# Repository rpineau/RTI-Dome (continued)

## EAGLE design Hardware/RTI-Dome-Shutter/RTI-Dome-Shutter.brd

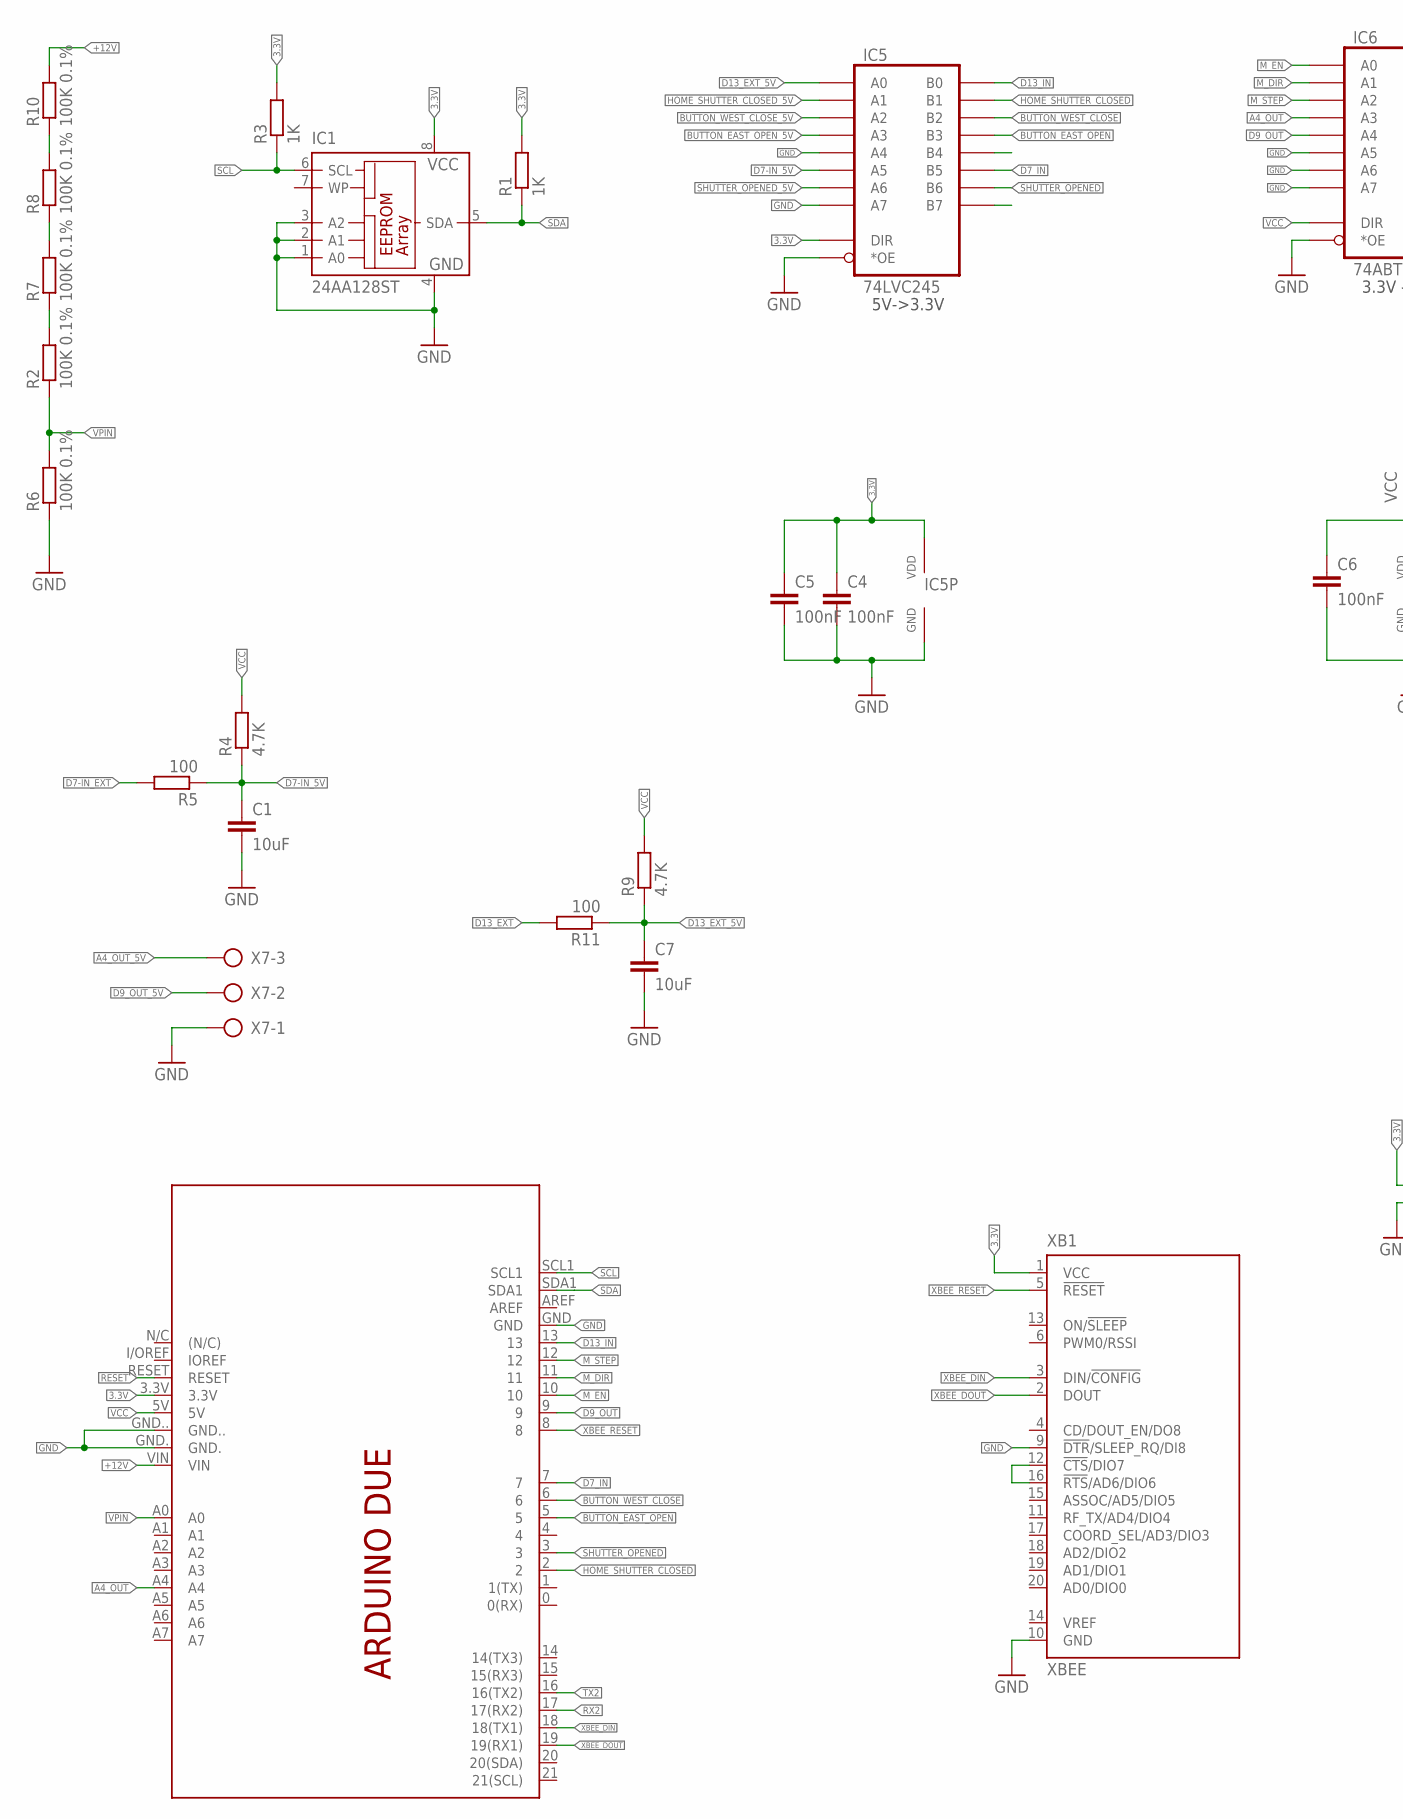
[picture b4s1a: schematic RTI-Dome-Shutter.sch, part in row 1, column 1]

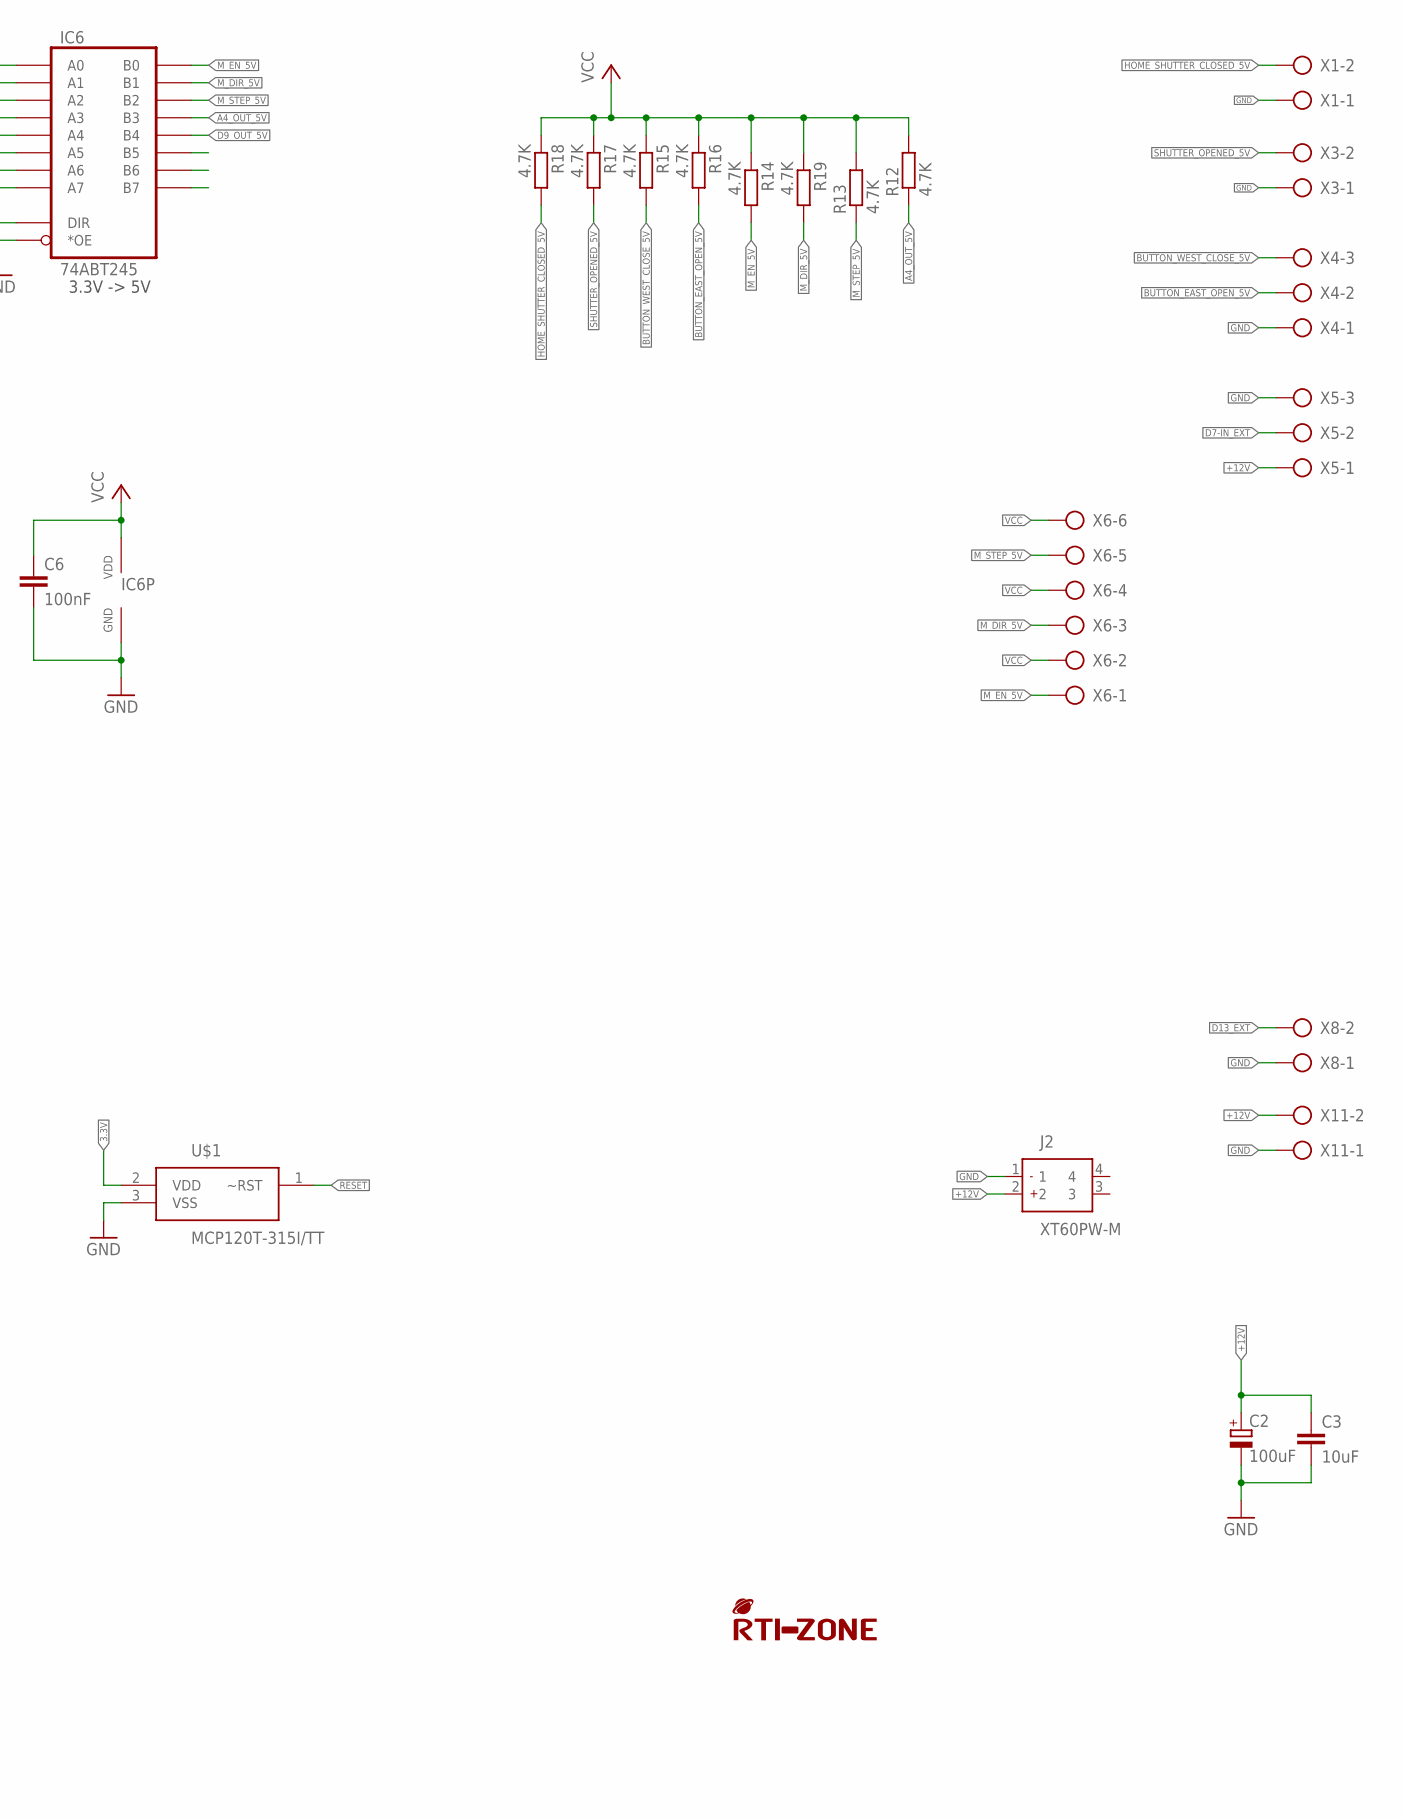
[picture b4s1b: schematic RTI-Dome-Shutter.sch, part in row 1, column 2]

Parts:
C1, C3, C7: 10uF; C0805
C2: 100uF; UD-10X10_NICHICON
C4, C5, C6: 100nF; C0805
IC1: 24AA128ST; TSSOP8
IC5: 74LVC245; TSSOP20
IC6: 74ABT245; TSSOP20
J2: XT60PW-M; XT60PWM
PCB1: ARDUINO_DUE_SHIELD_SHORT
R1, R3: 1K; R0805
R2, R6, R7, R8, R10: 100K 0.1%; R0805
R4, R9, R12, R13, R14, R15, R16, R17, R18, R19: 4.7K; R0805
R5, R11: 100; R0805
U$1: MCP120T-315I/TT; SOT95P237X112-3N; MPN MCP120T-315I/TT
U$4: RTI-LOGO_BIG; LOGO_BIG
X1, X3, X8, X11: AK500/2
X4, X5, X7: AK500/3
X6: AK500/6
XB1: XBEE

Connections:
3.3V: C4.1, C5.1, IC1.8 (VCC), IC5.P$1 (DIR), IC5.P$20 (VDD), PCB1.3.3V, R1.2, R3.2, U$1.2 (VDD), XB1.1 (VCC)
+12V: C2.+, C3.1, J2.2, PCB1.VIN, R10.2, X5.1, X11.2
A4_OUT: IC6.P$5 (A3), PCB1.A4
A4_OUT_5V: IC6.P$15 (B3), R12.1, X7.3
BUTTON_EAST_OPEN: IC5.P$15 (B3), PCB1.5
BUTTON_EAST_OPEN_5V: IC5.P$5 (A3), R16.2, X4.2
BUTTON_WEST_CLOSE: IC5.P$16 (B2), PCB1.6
BUTTON_WEST_CLOSE_5V: IC5.P$4 (A2), R15.2, X4.3
D7-IN_5V: C1.1, IC5.P$7 (A5), R4.1, R5.1
D7-IN_EXT: R5.2, X5.2
D7_IN: IC5.P$13 (B5), PCB1.7
D9_OUT: IC6.P$6 (A4), PCB1.9
D9_OUT_5V: IC6.P$14 (B4), X7.2
D13_EXT: R11.2, X8.2
D13_EXT_5V: C7.1, IC5.P$2 (A0), R9.1, R11.1
D13_IN: IC5.P$18 (B0), PCB1.13
GND: C1.2, C2.-, C3.2, C4.2, C5.2, C6.2, C7.2, IC1.1 (A0), IC1.2 (A1), IC1.3 (A2), IC1.4 (GND), IC5.P$6 (A4), IC5.P$9 (A7), IC5.P$10 (GND), IC5.P$19 (*OE), IC6.P$7 (A5), IC6.P$8 (A6), IC6.P$9 (A7), IC6.P$10 (GND), IC6.P$19 (*OE), J2.1, PCB1.GND, PCB1.GND., PCB1.GND.., R6.1, U$1.3 (VSS), X1.1, X3.1, X4.1, X5.3, X7.1, X8.1, X11.1, XB1.9 (!DTR!/SLEEP_RQ/DI8), XB1.10 (GND)
HOME_SHUTTER_CLOSED: IC5.P$17 (B1), PCB1.2
HOME_SHUTTER_CLOSED_5V: IC5.P$3 (A1), R18.2, X1.2
M_DIR: IC6.P$3 (A1), PCB1.11
M_DIR_5V: IC6.P$17 (B1), R19.2, X6.3
M_EN: IC6.P$2 (A0), PCB1.10
M_EN_5V: IC6.P$18 (B0), R14.2, X6.1
M_STEP: IC6.P$4 (A2), PCB1.12
M_STEP_5V: IC6.P$16 (B2), R13.1, X6.5
unnamed: R7.2, R8.1
unnamed: R8.2, R10.1
unnamed: R2.2, R7.1
unnamed: XB1.12 (!CTS!/DIO7), XB1.16 (!RTS!/AD6/DIO6)
RESET: PCB1.RESET, U$1.1 (~RST)
RX2: PCB1.17 (17(RX2))
SCL: IC1.6 (SCL), PCB1.SCL1, R3.1
SDA: IC1.5 (SDA), PCB1.SDA1, R1.1
SHUTTER_OPENED: IC5.P$12 (B6), PCB1.3
SHUTTER_OPENED_5V: IC5.P$8 (A6), R17.2, X3.2
TX2: PCB1.16 (16(TX2))
VCC: C6.1, IC6.P$1 (DIR), IC6.P$20 (VDD), PCB1.5V, R4.2, R9.2, R12.2, R13.2, R14.1, R15.1, R16.1, R17.1, R18.1, R19.1, X6.2, X6.4, X6.6
VPIN: PCB1.A0, R2.1, R6.2
XBEE_DIN: PCB1.18 (18(TX1)), XB1.3 (DIN/!CONFIG)
XBEE_DOUT: PCB1.19 (19(RX1)), XB1.2 (DOUT)
XBEE_RESET: PCB1.8, XB1.5 (!RESET)

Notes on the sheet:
5V->3.3V
3.3V -> 5V

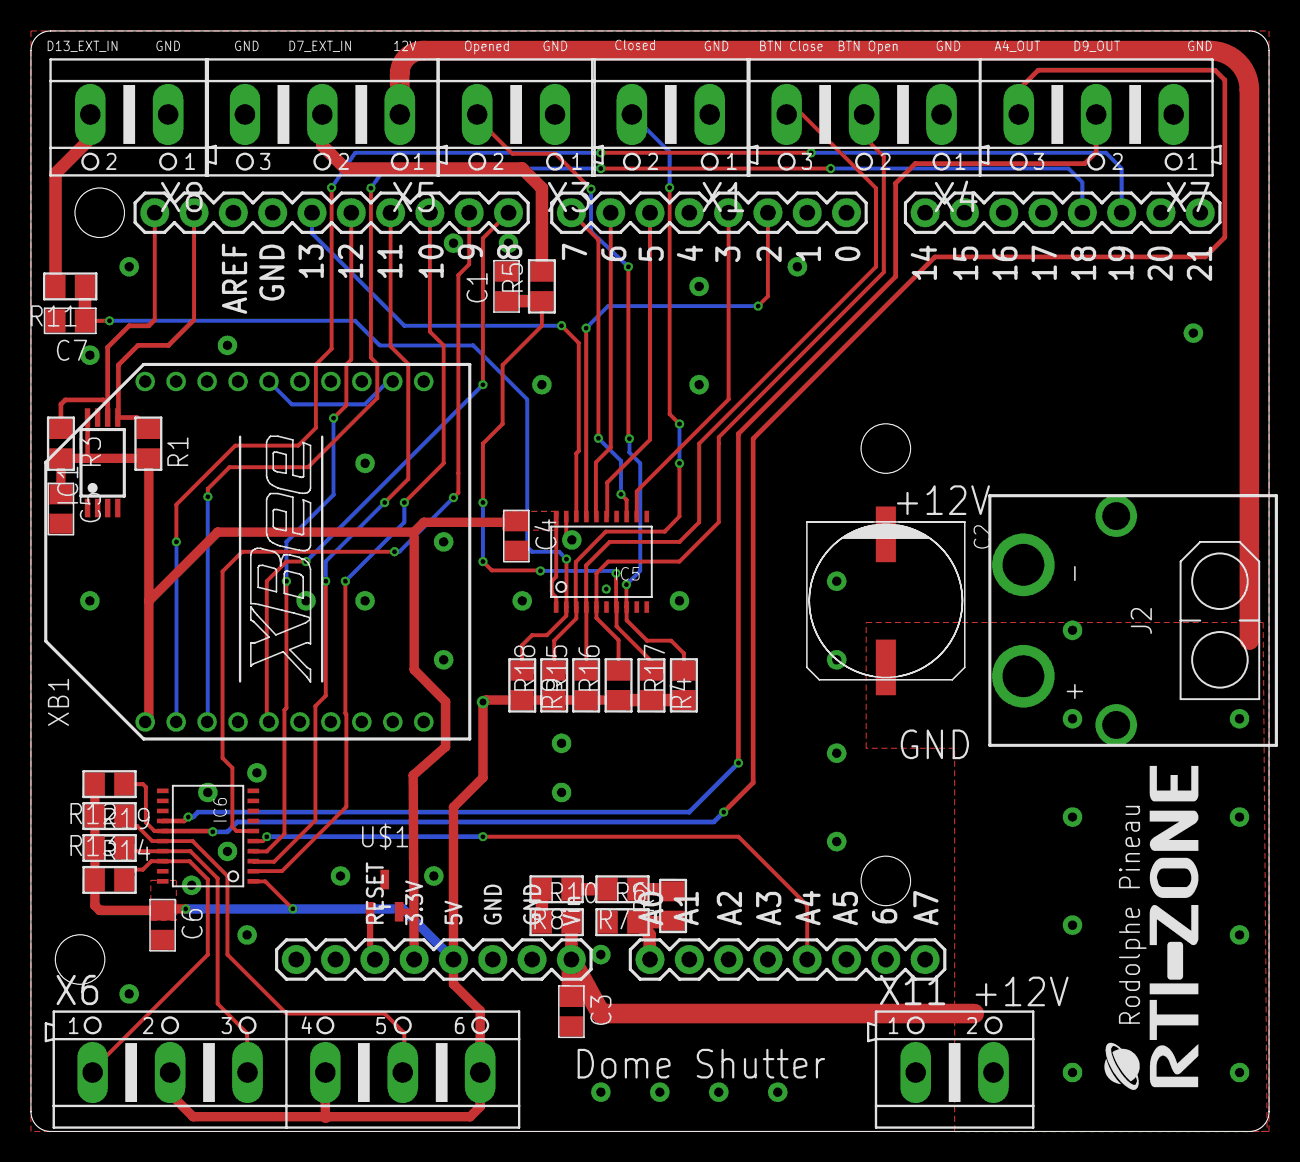
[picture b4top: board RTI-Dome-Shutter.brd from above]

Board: 2 copper layers, 80.0 x 71.1 mm, 42 parts (0 on the bottom side), 39 nets.

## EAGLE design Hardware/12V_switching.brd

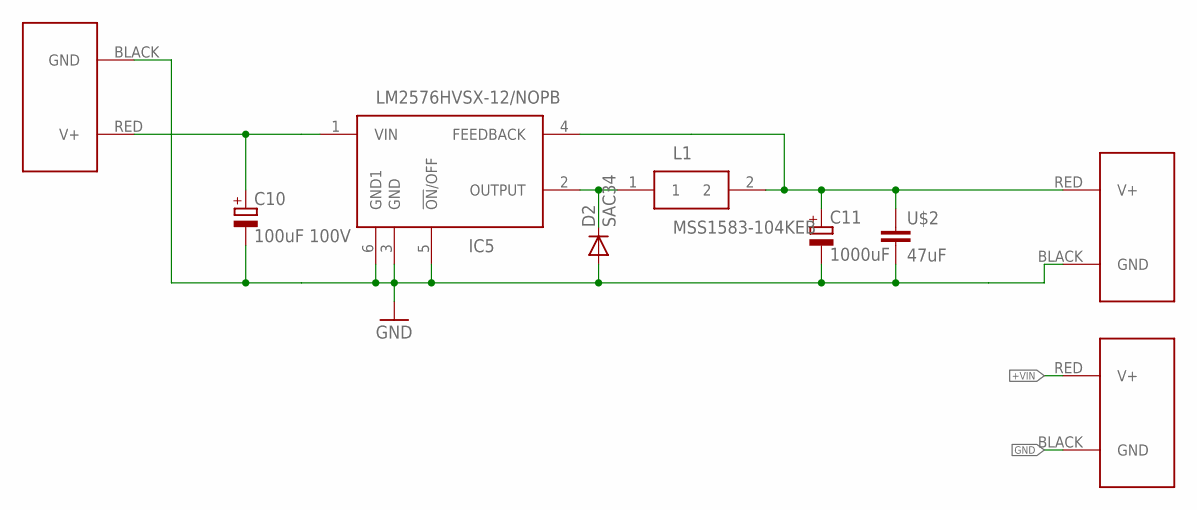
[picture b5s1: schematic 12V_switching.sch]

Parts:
C10: 100uF 100V; UD-10X10_NICHICON
C11: 1000uF; UD-10X10_NICHICON
D2: SAC34; DO-214AC
IC5: LM2576HVSX-12/NOPB; TO263-5; MOUSER_PART_NUMBER LM2576HVSX-12/NOPB
J1, J2, J3: POWERPOLE_POWER45A; POWERPOLE_PAIR_45A
L1: MSS1583-104KEB; INDPM150150X860N
U$2: 47uF; C1206

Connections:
12VOUT: D2.C, IC5.2 (OUTPUT), L1.1
+12V: C11.+, IC5.4 (FEEDBACK), J2.RED (V+), L1.2, U$2.1
+VIN: C10.+, IC5.1 (VIN), J1.RED (V+), J3.RED (V+)
GND: C10.-, C11.-, D2.A, IC5.3 (GND), IC5.5 (!ON!/OFF), IC5.6 (GND1), J1.BLACK (GND), J2.BLACK (GND), J3.BLACK (GND), U$2.2

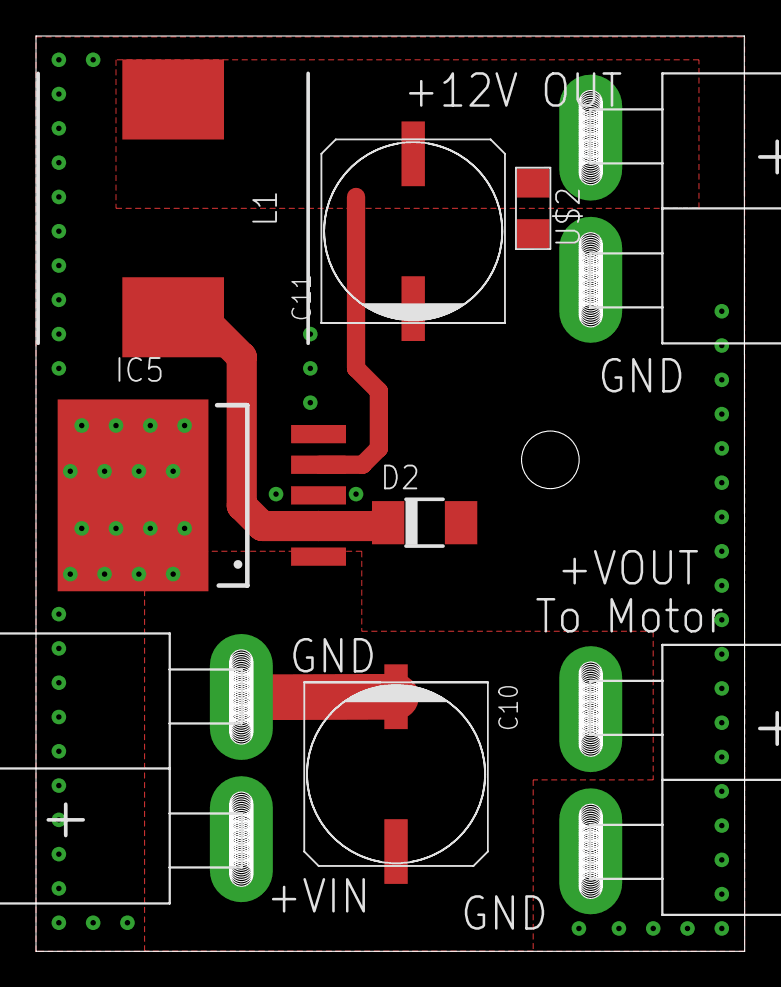
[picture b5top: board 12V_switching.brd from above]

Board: 2 copper layers, 39.4 x 50.9 mm, 9 parts (0 on the bottom side), 4 nets.

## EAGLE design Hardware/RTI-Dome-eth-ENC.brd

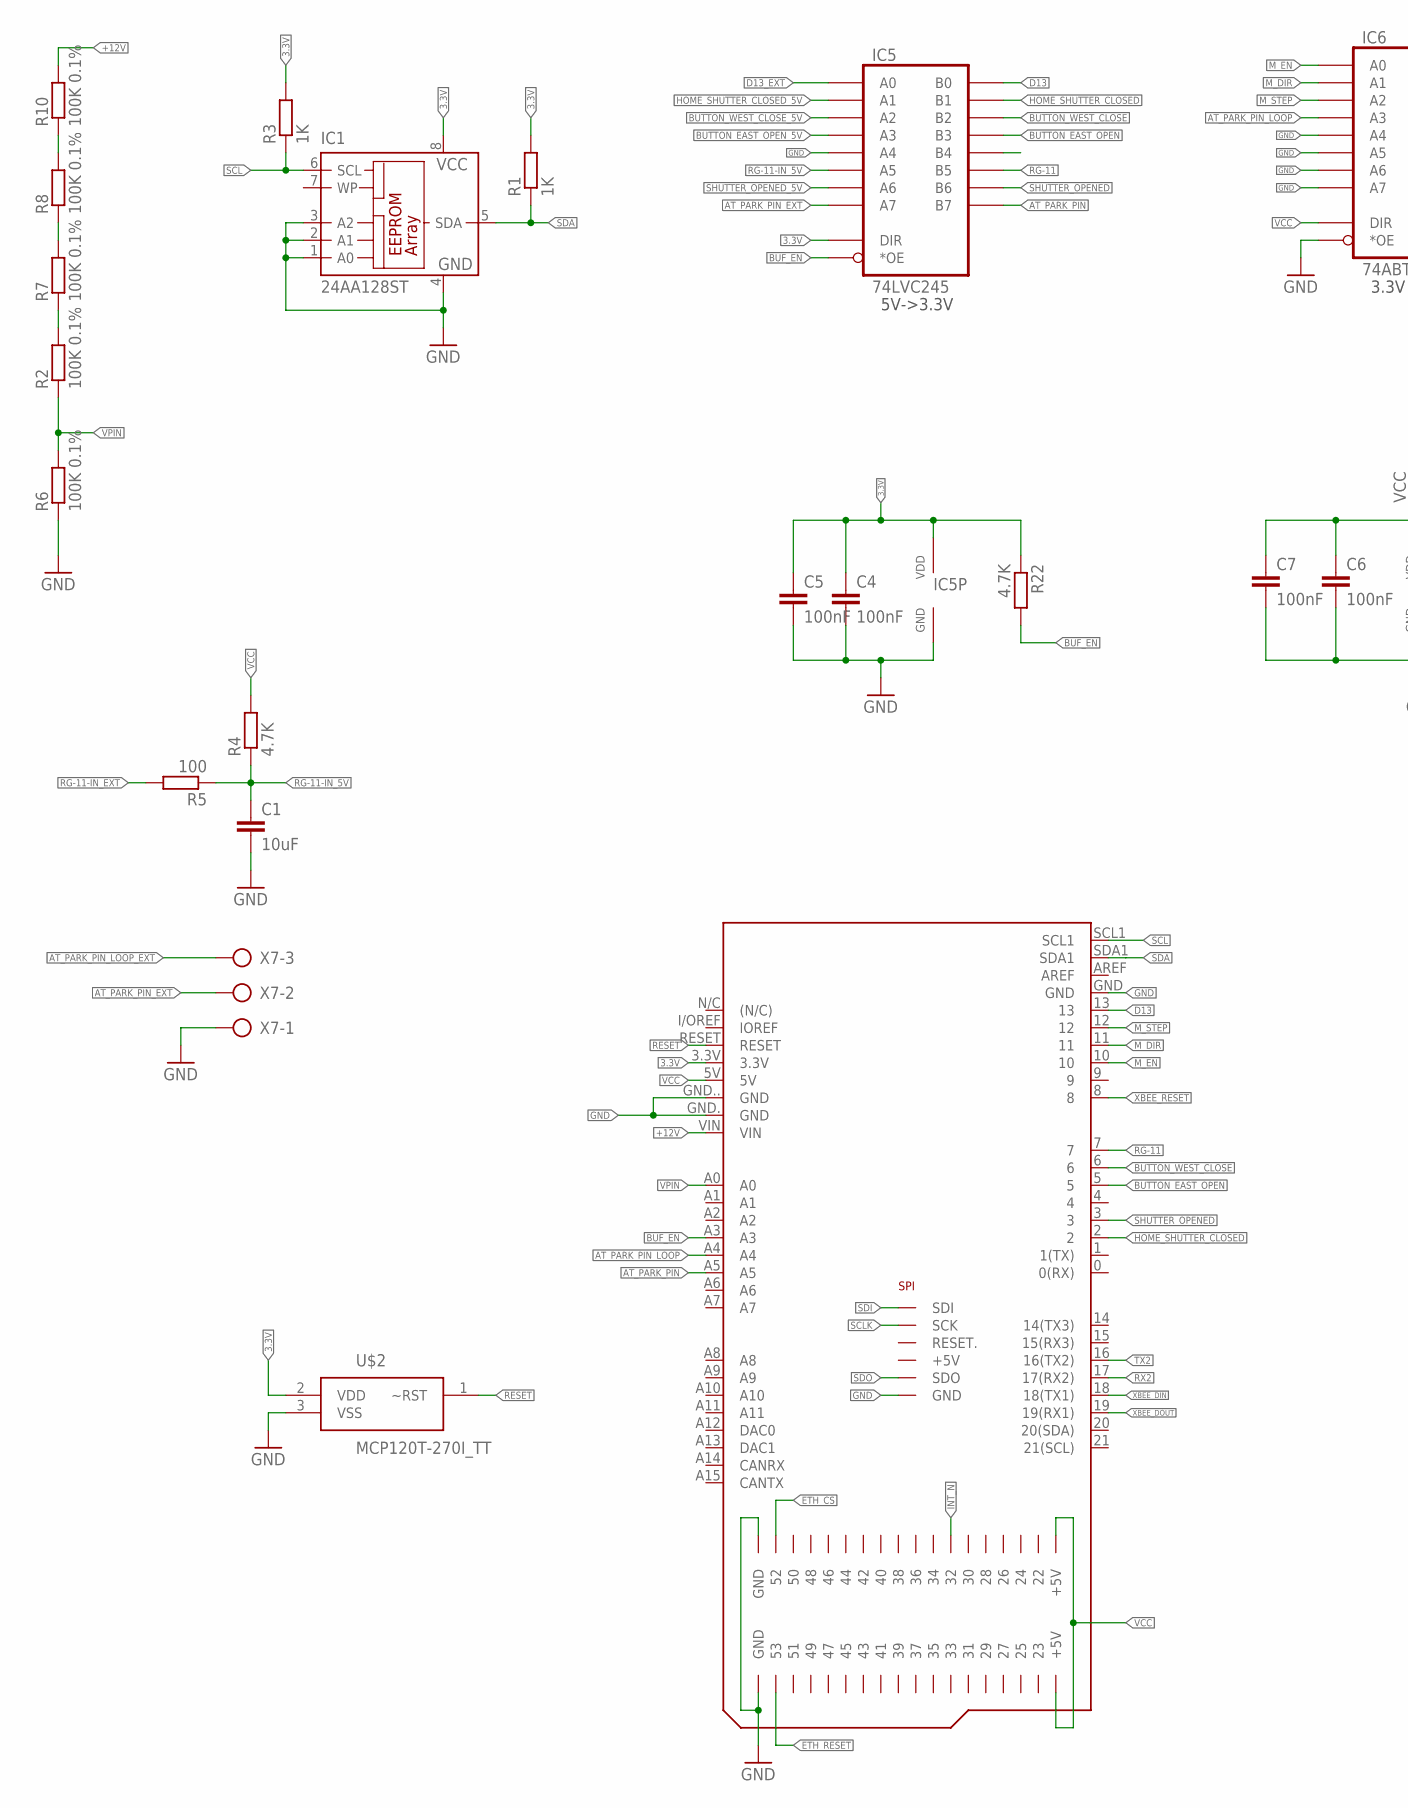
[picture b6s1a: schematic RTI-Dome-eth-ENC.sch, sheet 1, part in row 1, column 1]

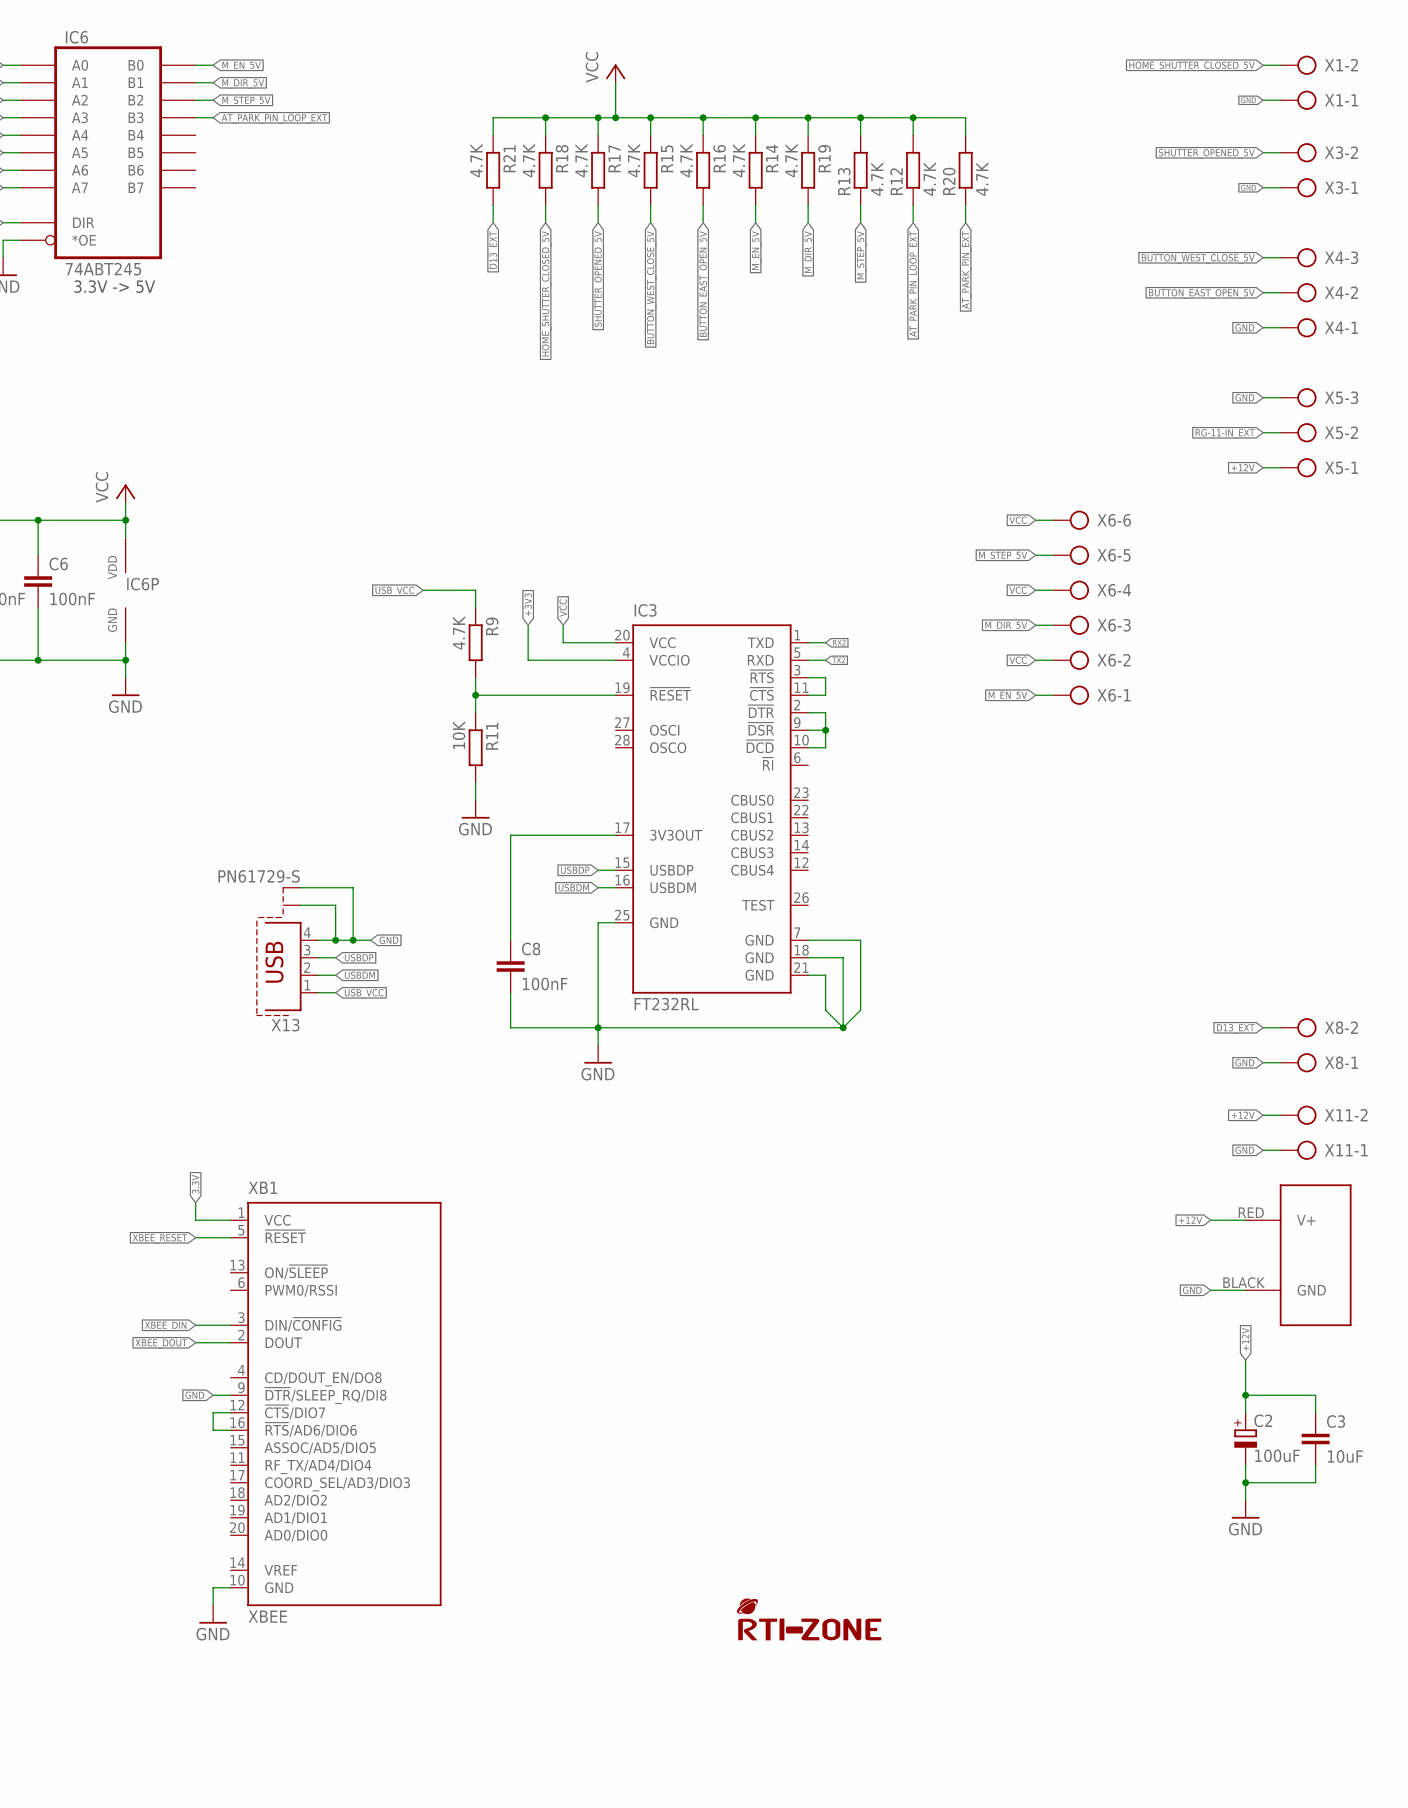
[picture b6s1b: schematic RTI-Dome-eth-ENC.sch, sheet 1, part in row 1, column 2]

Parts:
C1, C3: 10uF; C0805
C2: 100uF; UD-10X10_NICHICON
C4, C5, C6, C7, C8: 100nF; C0805
IC1: 24AA128ST; TSSOP8
IC3: FT232RL; SSOP28
IC5: 74LVC245; TSSOP20; MPN 74LVC245APW,118
IC6: 74ABT245; TSSOP20; MPN SN74ABT245BDWR
J1: POWERPOLE_POWER45A; POWERPOLE_PAIR_45A
R1, R3: 1K; R0805
R2, R6, R7, R8, R10: 100K 0.1%; R0805
R4, R9, R12, R13, R14, R15, R16, R17, R18, R19, R20, R21, R22: 4.7K; R0805
R5: 100; R0805
R11: 10K; R0805
U$1: ARDUINO_DUE_SHIELD_FULL
U$2: MCP120T-270I_TT; SOT95P237X112-3N; MPN MCP120T-270I/TT
U$4: RTI-LOGO_BIG; LOGO_BIG
X1, X3, X8, X11: AK500/2
X4, X5, X7: AK500/3
X6: AK500/6
X13: PN61729-S
XB1: XBEE

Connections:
3.3V: C4.1, C5.1, IC1.8 (VCC), IC5.P$1 (DIR), IC5.P$20 (VDD), R1.2, R3.2, R22.1, U$1.3.3V, U$2.2 (VDD), XB1.1 (VCC)
+3V3: IC3.4 (VCCIO); also elsewhere on the board
+5V: U$1.+5V_ (+5V)
+12V: C2.+, C3.1, J1.RED (V+), R10.2, U$1.VIN, X5.1, X11.2
AT_PARK_PIN: IC5.P$11 (B7), U$1.A5
AT_PARK_PIN_EXT: IC5.P$9 (A7), R20.1, X7.2
AT_PARK_PIN_LOOP: IC6.P$5 (A3), U$1.A4
AT_PARK_PIN_LOOP_EXT: IC6.P$15 (B3), R12.1, X7.3
BUF_EN: IC5.P$19 (*OE), R22.2, U$1.A3
BUTTON_EAST_OPEN: IC5.P$15 (B3), U$1.5
BUTTON_EAST_OPEN_5V: IC5.P$5 (A3), R16.2, X4.2
BUTTON_WEST_CLOSE: IC5.P$16 (B2), U$1.6
BUTTON_WEST_CLOSE_5V: IC5.P$4 (A2), R15.2, X4.3
D13: IC5.P$18 (B0), U$1.13
D13_EXT: IC5.P$2 (A0), R21.2, X8.2
DTR_DSR_DCD: IC3.2 (!DTR), IC3.9 (!DSR), IC3.10 (!DCD)
ETH_CS: U$1.52; also elsewhere on the board
ETH_RESET: U$1.53
GND: C1.2, C2.-, C3.2, C4.2, C5.2, C6.2, C7.2, C8.2, IC1.1 (A0), IC1.2 (A1), IC1.3 (A2), IC1.4 (GND), IC3.7 (GND), IC3.18 (GND), IC3.21 (GND), IC3.25 (GND), IC5.P$6 (A4), IC5.P$10 (GND), IC6.P$6 (A4), IC6.P$7 (A5), IC6.P$8 (A6), IC6.P$9 (A7), IC6.P$10 (GND), IC6.P$19 (*OE), J1.BLACK (GND), R6.1, R11.2, U$1.GND, U$1.GND. (GND), U$1.GND.. (GND), U$1.GND... (GND), U$1.GND.... (GND), U$1.GND__ (GND), U$2.3 (VSS), X1.1, X3.1, X4.1, X5.3, X7.1, X8.1, X11.1, X13.4, X13.S1, X13.S2, XB1.9 (!DTR!/SLEEP_RQ/DI8), XB1.10 (GND); also elsewhere on the board
HOME_SHUTTER_CLOSED: IC5.P$17 (B1), U$1.2
HOME_SHUTTER_CLOSED_5V: IC5.P$3 (A1), R18.2, X1.2
INT_N: U$1.32; also elsewhere on the board
M_DIR: IC6.P$3 (A1), U$1.11
M_DIR_5V: IC6.P$17 (B1), R19.2, X6.3
M_EN: IC6.P$2 (A0), U$1.10
M_EN_5V: IC6.P$18 (B0), R14.2, X6.1
M_STEP: IC6.P$4 (A2), U$1.12
M_STEP_5V: IC6.P$16 (B2), R13.1, X6.5
unnamed: IC3.19 (!RESET), R9.2, R11.1
unnamed: R7.2, R8.1
unnamed: R8.2, R10.1
unnamed: R2.2, R7.1
unnamed: C8.1, IC3.17 (3V3OUT)
unnamed: XB1.12 (!CTS!/DIO7), XB1.16 (!RTS!/AD6/DIO6)
RESET: U$1.RESET, U$2.1 (~RST)
RG-11: IC5.P$13 (B5), U$1.7
RG-11-IN_5V: C1.1, IC5.P$7 (A5), R4.1, R5.1
RG-11-IN_EXT: R5.2, X5.2
RTS_CTS: IC3.3 (!RTS), IC3.11 (!CTS)
RX2: IC3.1 (TXD), U$1.17 (17(RX2))
SCL: IC1.6 (SCL), R3.1, U$1.SCL1
SCLK: U$1.SCK; also elsewhere on the board
SDA: IC1.5 (SDA), R1.1, U$1.SDA1
SDI: U$1.MISO (SDI); also elsewhere on the board
SDO: U$1.MOSI (SDO); also elsewhere on the board
SHUTTER_OPENED: IC5.P$12 (B6), U$1.3
SHUTTER_OPENED_5V: IC5.P$8 (A6), R17.2, X3.2
TX2: IC3.5 (RXD), U$1.16 (16(TX2))
USBDM: IC3.16 (USBDM), X13.2
USBDP: IC3.15 (USBDP), X13.3
USB_VCC: R9.1, X13.1
VCC: C6.1, C7.1, IC3.20 (VCC), IC6.P$1 (DIR), IC6.P$20 (VDD), R4.2, R12.2, R13.2, R14.1, R15.1, R16.1, R17.1, R18.1, R19.1, R20.2, R21.1, U$1.5V, U$1.5V. (+5V), U$1.5V.. (+5V), X6.2, X6.4, X6.6; also elsewhere on the board
VPIN: R2.1, R6.2, U$1.A0
XBEE_DIN: U$1.18 (18(TX1)), XB1.3 (DIN/!CONFIG)
XBEE_DOUT: U$1.19 (19(RX1)), XB1.2 (DOUT)
XBEE_RESET: U$1.8, XB1.5 (!RESET)

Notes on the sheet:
5V->3.3V
3.3V -> 5V

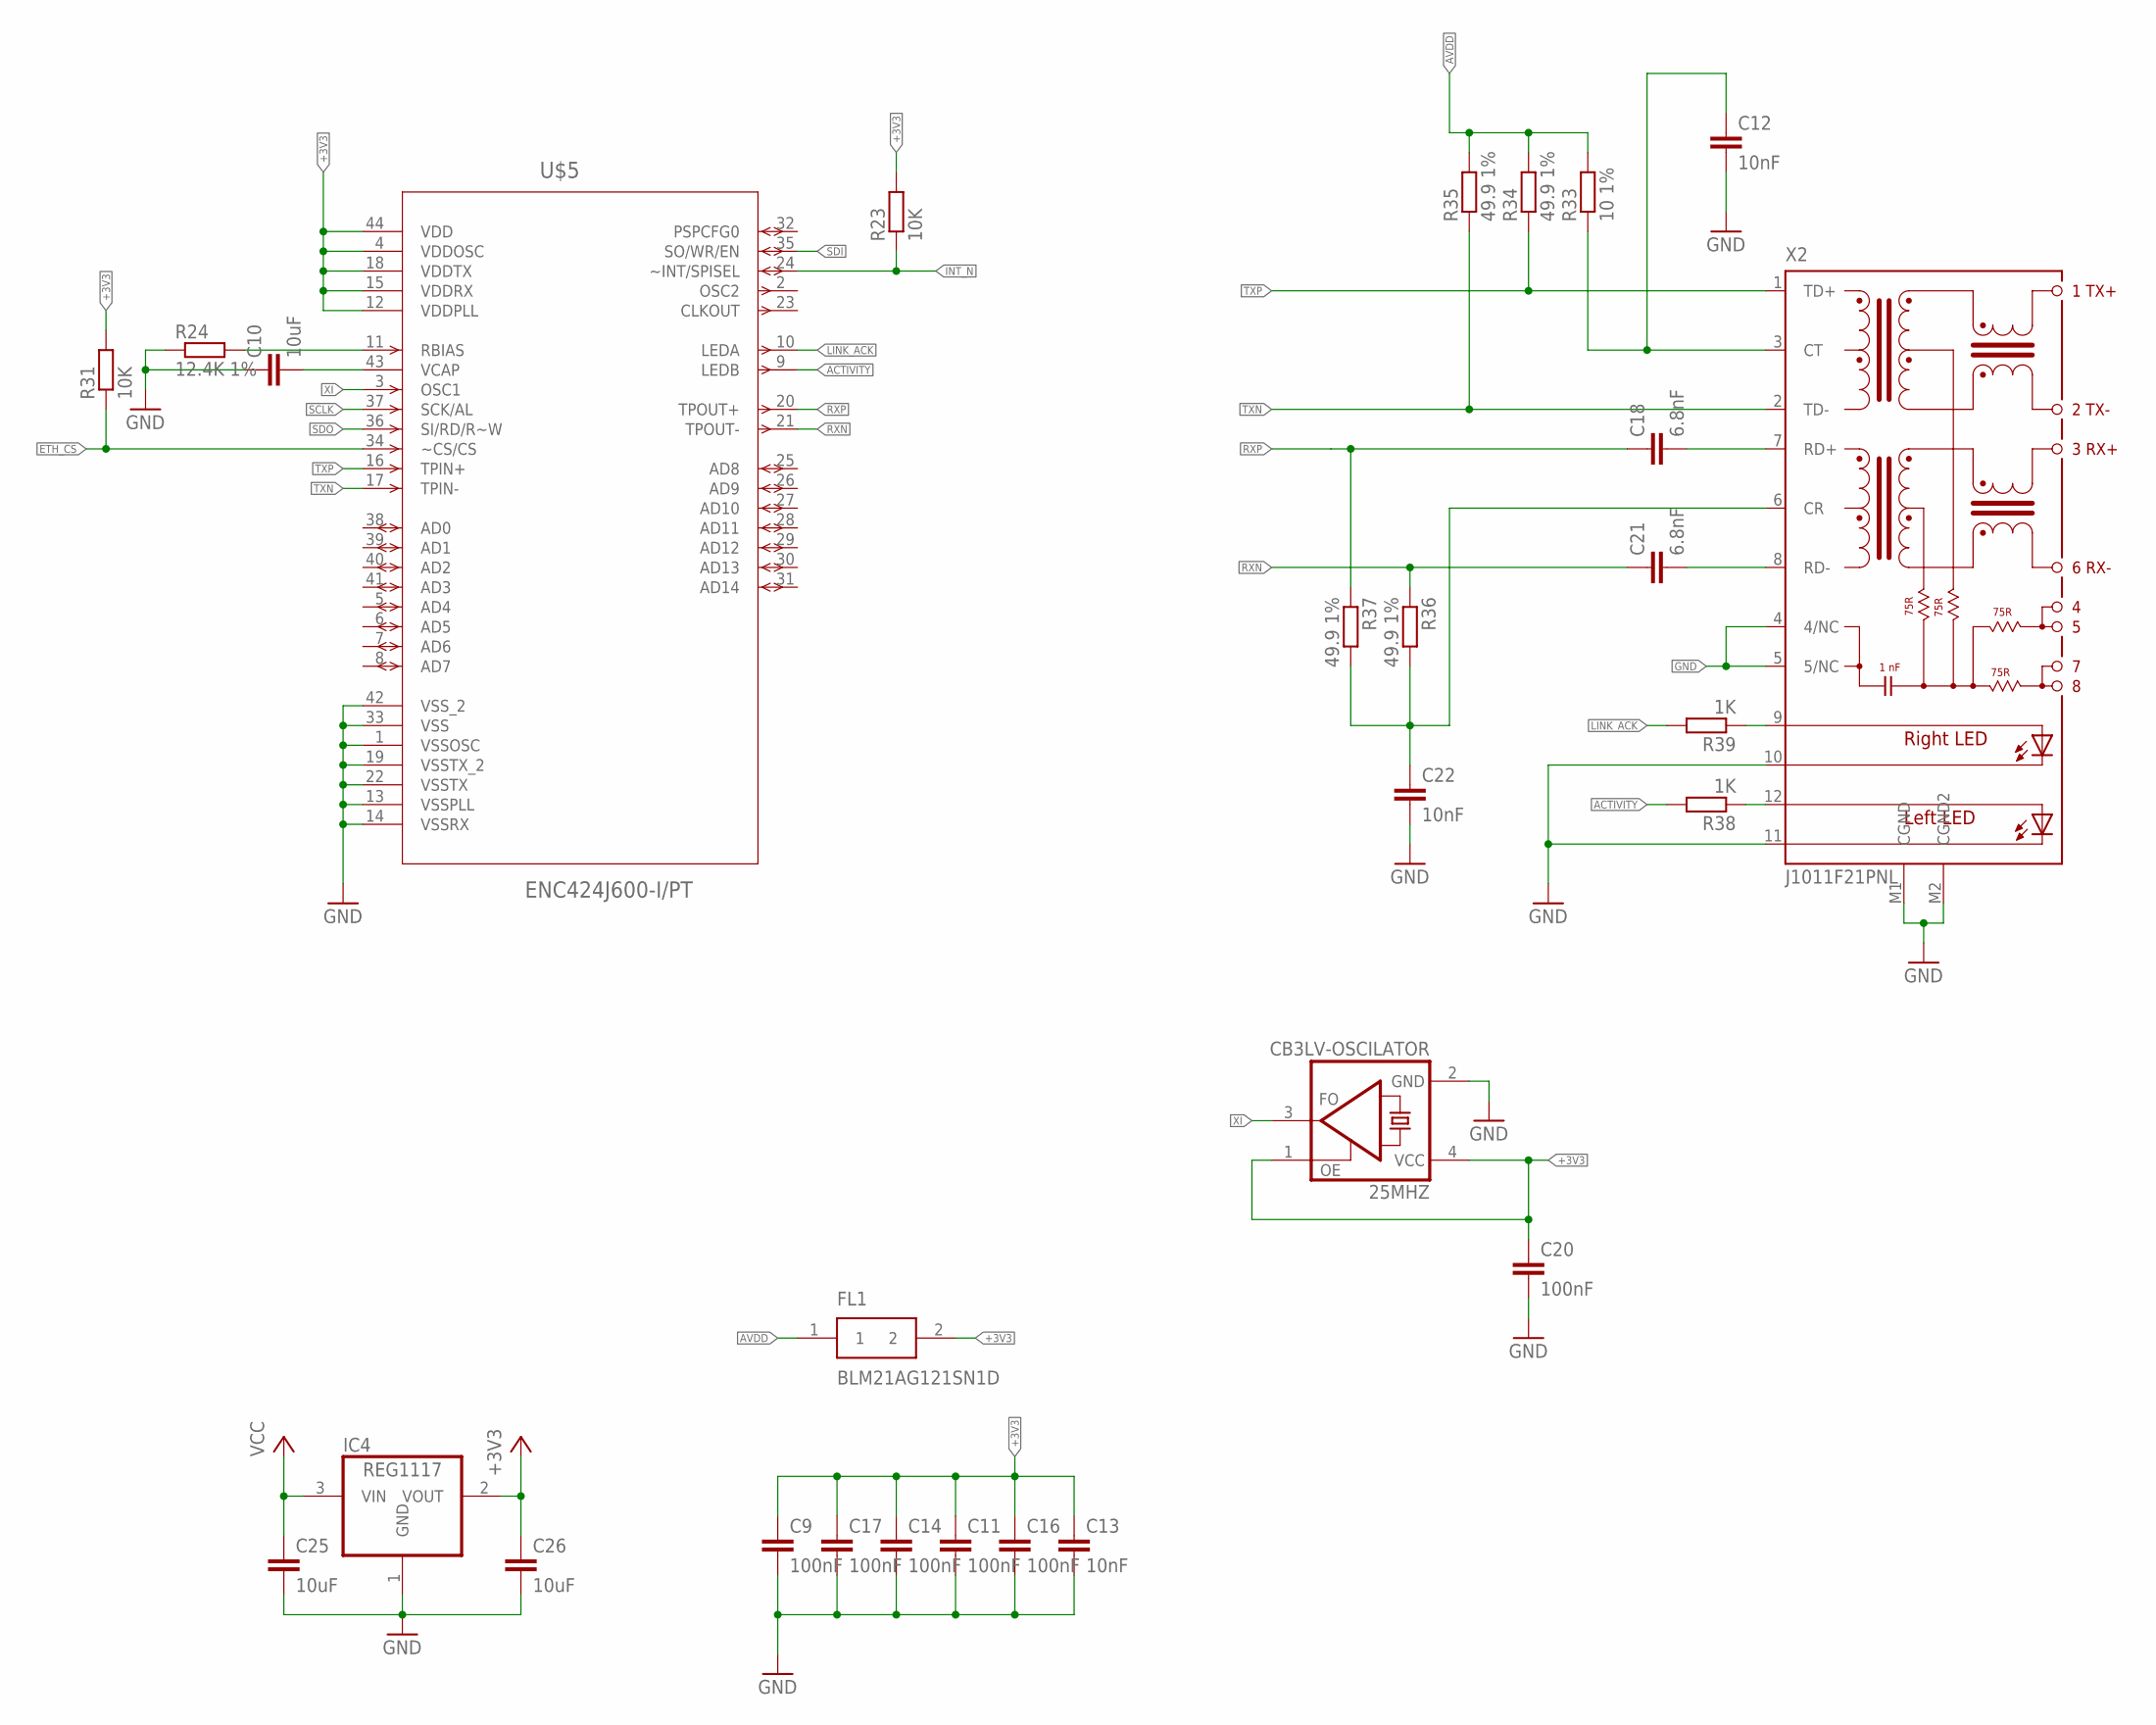
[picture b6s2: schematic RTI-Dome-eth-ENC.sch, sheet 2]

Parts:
25MHZ: CB3LV-OSCILATOR; SMD-7050_4P; MPN O705025MEDH4MI
C9, C11, C14, C16, C17, C20: 100nF; C0805
C10: 10uF; C0805
C12, C13, C22: 10nF; C0805
C18, C21: 6.8nF; C0805
C25, C26: 10uF; C1206
FL1: BLM21AG121SN1D; L0805
IC4: REG1117; SOT223; MPN REG1117-3.3/2K5
R23, R31: 10K; R0805
R24: 12.4K 1%; R0805
R33: 10 1%; R0805
R34, R35, R36, R37: 49.9 1%; R0805
R38, R39: 1K; R0805
U$5: ENC424J600-I/PT; QFP50P1200X1200X120-44N; MPN ENC424J600-I/PT
X2: J1011F21PNL; J1

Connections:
+3V3: 25MHZ.1 (OE), 25MHZ.4 (VDD), C9.1, C11.1, C13.1, C14.1, C16.1, C17.1, C20.1, C26.1, FL1.2, IC4.2 (VOUT), R23.2, R31.2, U$5.4 (VDDOSC), U$5.12 (VDDPLL), U$5.15 (VDDRX), U$5.18 (VDDTX), U$5.44 (VDD); also elsewhere on the board
ACTIVITY: R38.2, U$5.9 (LEDB)
AVDD: FL1.1, R33.2, R34.2, R35.2
ETH_CS: R31.1, U$5.34 (~CS/CS); also elsewhere on the board
GND: 25MHZ.2 (GND), C9.2, C10.1, C11.2, C12.2, C13.2, C14.2, C16.2, C17.2, C20.2, C22.2, C25.2, C26.2, IC4.1 (GND), R24.1, U$5.1 (VSSOSC), U$5.13 (VSSPLL), U$5.14 (VSSRX), U$5.19 (VSSTX_2), U$5.22 (VSSTX), U$5.33 (VSS), U$5.42 (VSS_2), X2.4 (4/NC), X2.5 (5/NC), X2.10 (C-R), X2.11 (C-L), X2.M1 (CGND), X2.M2 (CGND2); also elsewhere on the board
INT_N: R23.1, U$5.24 (~INT/SPISEL); also elsewhere on the board
LINK_ACK: R39.2, U$5.10 (LEDA)
unnamed: R24.2, U$5.11 (RBIAS)
unnamed: C10.2, U$5.43 (VCAP)
unnamed: R39.1, X2.9 (A-R)
unnamed: C22.1, R36.2, R37.2, X2.6 (CR)
unnamed: R38.1, X2.12 (AL)
unnamed: C18.2, X2.7 (RD+)
unnamed: C21.2, X2.8 (RD-)
unnamed: C12.1, R33.1, X2.3 (CT)
RXN: C21.1, R36.1, U$5.21 (TPOUT-)
RXP: C18.1, R37.1, U$5.20 (TPOUT+)
SCLK: U$5.37 (SCK/AL); also elsewhere on the board
SDI: U$5.35 (SO/WR/EN); also elsewhere on the board
SDO: U$5.36 (SI/RD/R~W); also elsewhere on the board
TXN: R35.1, U$5.17 (TPIN-), X2.2 (TD-)
TXP: R34.1, U$5.16 (TPIN+), X2.1 (TD+)
VCC: C25.1, IC4.3 (VIN); also elsewhere on the board
XI: 25MHZ.3 (FO), U$5.3 (OSC1)
